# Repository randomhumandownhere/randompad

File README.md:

# randompad
randompad is @randomhumandownhere 's submission to the Hackpad YSWS. it has 9 keys, 16 WS2812B LEDs and a 0.91in SSD1306 OLED display (fancy graphics!) as well as an EC11 rotary encoder. it uses KMK firmware too.

## features
- really simple 3d printed case
- 128x32 OLED display
- 16 WS2812B LEDs
- 9 MX style keys
- and an EC11 rotary encoder! 

## cad model!

it uses 4 M3 bolts and heatset inserts to hold it together

## pcb and schematics!

## notes?
i'll probably make a better, more polished one in the future with more features

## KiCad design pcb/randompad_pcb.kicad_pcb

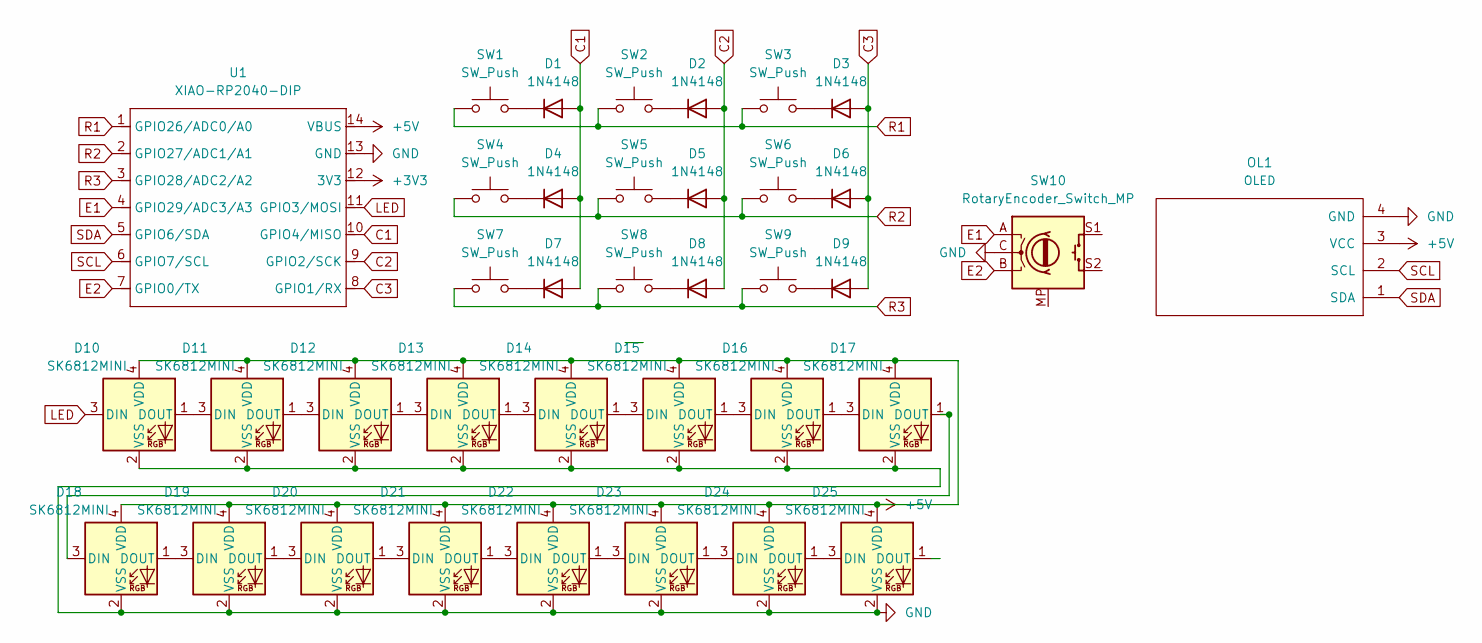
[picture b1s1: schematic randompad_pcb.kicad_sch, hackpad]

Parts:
D1, D2, D3, D4, D5, D6, D7, D8, D9: 1N4148; D_DO-35_SOD27_P7.62mm_Horizontal
D10, D11, D12, D13, D14, D15, D16, D17, D18, D19, D20, D21, D22, D23, D24, D25: SK6812MINI; LED_SK6812MINI_PLCC4_3.5x3.5mm_P1.75mm_[3D]
OL1: OLED
SW1, SW2, SW3, SW4, SW5, SW6, SW7, SW8, SW9: SW_Push; SW_Cherry_MX_1.00u_PCB_[3D]
SW10: RotaryEncoder_Switch_MP; RotaryEncoder_Alps_EC11E-Switch_Vertical_H20mm
U1: XIAO-RP2040-DIP

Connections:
+3V3: U1.12 (3V3)
+5V: D10.4 (VDD), D11.4 (VDD), D12.4 (VDD), D13.4 (VDD), D14.4 (VDD), D15.4 (VDD), D16.4 (VDD), D17.4 (VDD), D18.4 (VDD), D19.4 (VDD), D20.4 (VDD), D21.4 (VDD), D22.4 (VDD), D23.4 (VDD), D24.4 (VDD), D25.4 (VDD), OL1.3 (VCC), U1.14 (VBUS)
C1: D1.2 (A), D4.2 (A), D7.2 (A), U1.10 (GPIO4/MISO)
C2: D2.2 (A), D5.2 (A), D8.2 (A), U1.9 (GPIO2/SCK)
C3: D3.2 (A), D6.2 (A), D9.2 (A), U1.8 (GPIO1/RX)
E1: SW10.A, U1.4 (GPIO29/ADC3/A3)
E2: SW10.B, U1.7 (GPIO0/TX)
GND: D10.2 (VSS), D11.2 (VSS), D12.2 (VSS), D13.2 (VSS), D14.2 (VSS), D15.2 (VSS), D16.2 (VSS), D17.2 (VSS), D18.2 (VSS), D19.2 (VSS), D20.2 (VSS), D21.2 (VSS), D22.2 (VSS), D23.2 (VSS), D24.2 (VSS), D25.2 (VSS), OL1.4 (GND), SW10.C, U1.13 (GND)
LED: D10.3 (DIN), U1.11 (GPIO3/MOSI)
unnamed: D1.1 (K), SW1.2
unnamed: D2.1 (K), SW2.2
unnamed: D3.1 (K), SW3.2
unnamed: D4.1 (K), SW4.2
unnamed: D5.1 (K), SW5.2
unnamed: D6.1 (K), SW6.2
unnamed: D7.1 (K), SW7.2
unnamed: D8.1 (K), SW8.2
unnamed: D9.1 (K), SW9.2
unnamed: D10.1 (DOUT), D11.3 (DIN)
unnamed: D11.1 (DOUT), D12.3 (DIN)
unnamed: D12.1 (DOUT), D13.3 (DIN)
unnamed: D13.1 (DOUT), D14.3 (DIN)
unnamed: D14.1 (DOUT), D15.3 (DIN)
unnamed: D15.1 (DOUT), D16.3 (DIN)
unnamed: D16.1 (DOUT), D17.3 (DIN)
unnamed: D17.1 (DOUT), D18.3 (DIN)
unnamed: D18.1 (DOUT), D19.3 (DIN)
unnamed: D19.1 (DOUT), D20.3 (DIN)
unnamed: D20.1 (DOUT), D21.3 (DIN)
unnamed: D21.1 (DOUT), D22.3 (DIN)
unnamed: D22.1 (DOUT), D23.3 (DIN)
unnamed: D23.1 (DOUT), D24.3 (DIN)
unnamed: D24.1 (DOUT), D25.3 (DIN)
R1: SW1.1, SW2.1, SW3.1, U1.1 (GPIO26/ADC0/A0)
R2: SW4.1, SW5.1, SW6.1, U1.2 (GPIO27/ADC1/A1)
R3: SW7.1, SW8.1, SW9.1, U1.3 (GPIO28/ADC2/A2)
SCL: OL1.2 (SCL), U1.6 (GPIO7/SCL)
SDA: OL1.1 (SDA), U1.5 (GPIO6/SDA)

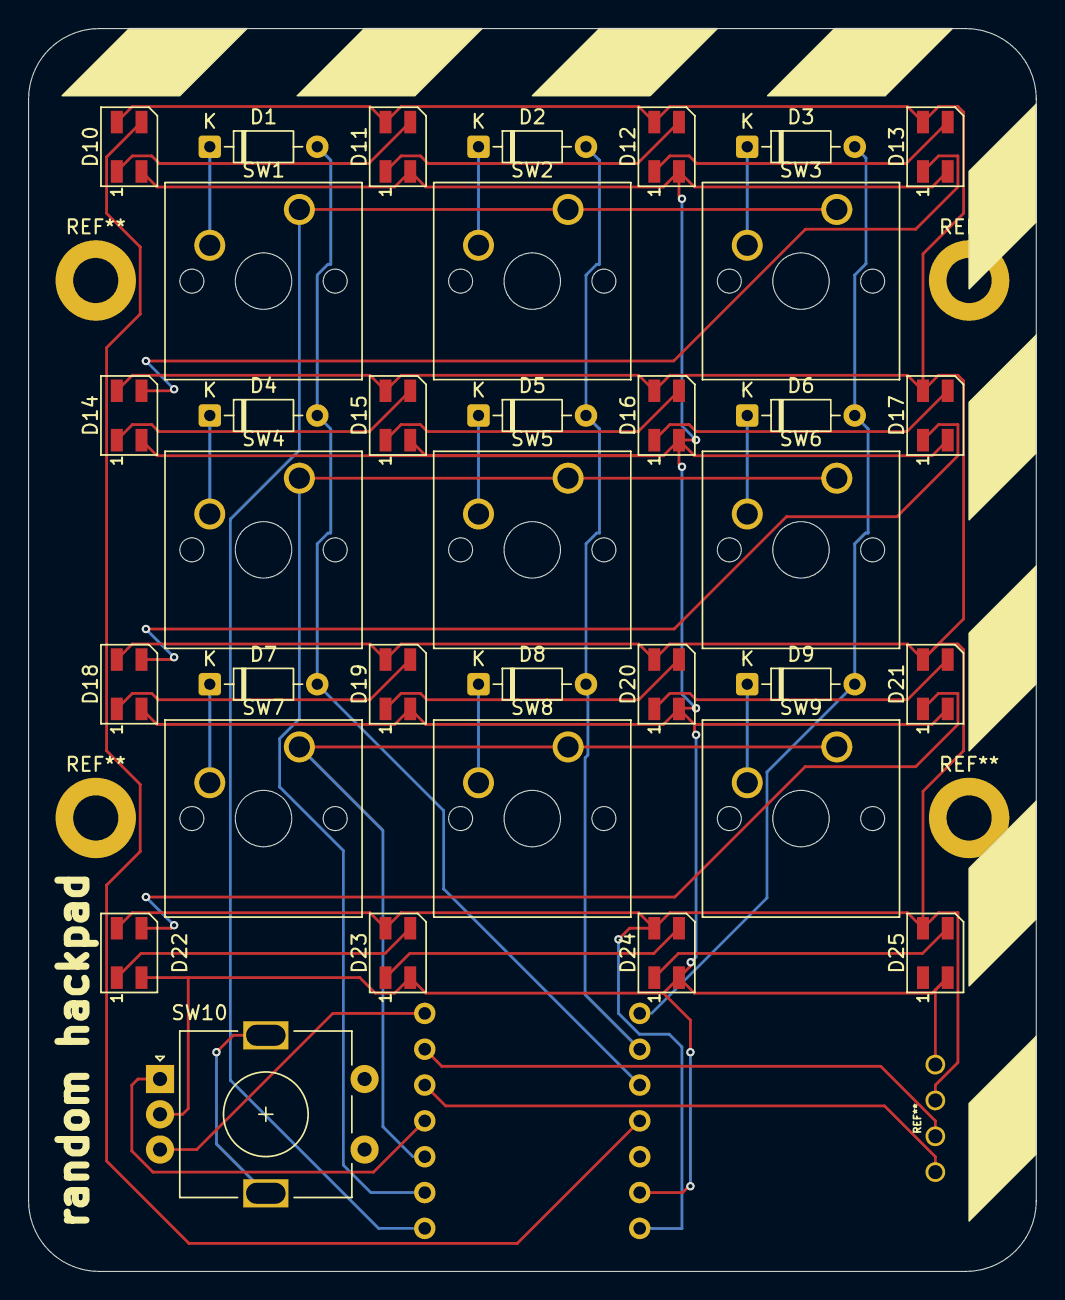
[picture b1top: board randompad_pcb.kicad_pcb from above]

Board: 2 copper layers, 71.4 x 88.1 mm, 37 parts (1 on the bottom side), 37 nets.

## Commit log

2025-06-28 oh right. the hackpad. the pad for hacking, the pad especially for hacking, the hack pad. that hackpad?
2025-06-28 updated output directory
